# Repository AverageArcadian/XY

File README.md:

# XY
ESP32 based XY motion controller for laser or plotting based machines

view here - https://kicanvas.org/?github=https%3A%2F%2Fgithub.com%2FAverageArcadian%2FXY

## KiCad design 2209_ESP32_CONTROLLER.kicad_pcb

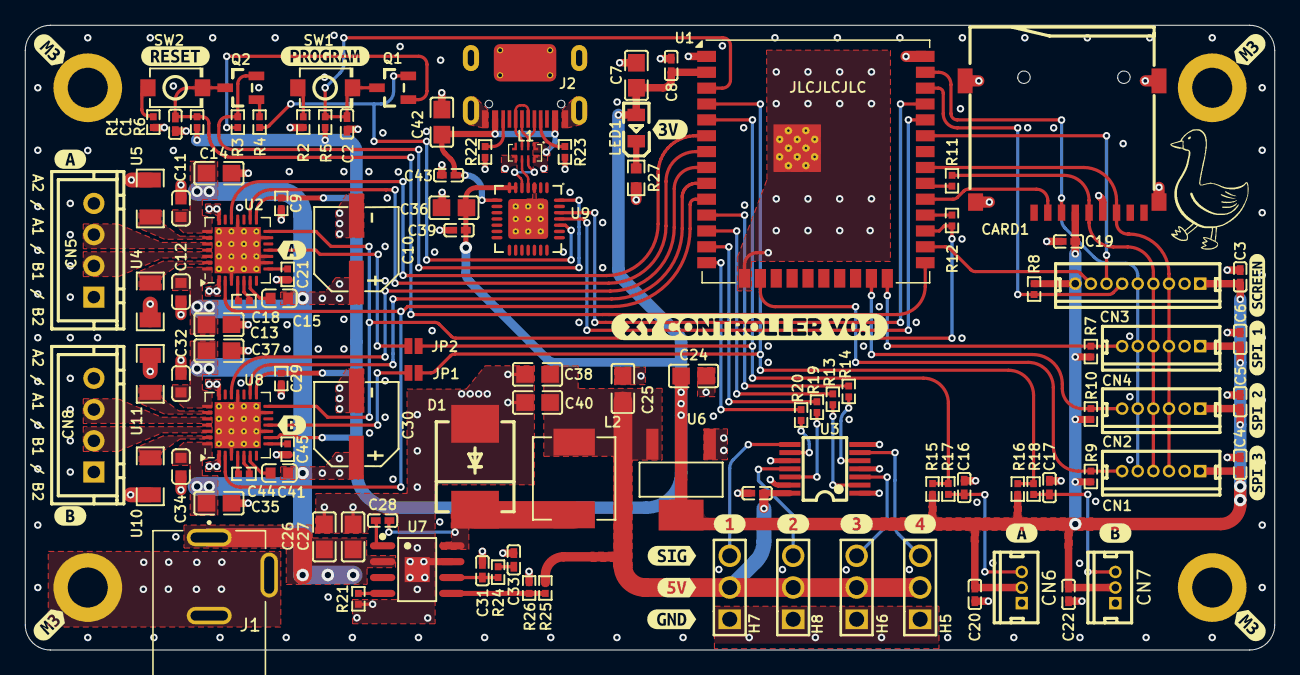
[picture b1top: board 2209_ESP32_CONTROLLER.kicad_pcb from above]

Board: 4 copper layers, 100.0 x 50.0 mm, 137 parts (0 on the bottom side), 84 nets.

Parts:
C1, C2, C3, C4, C5, C6, C8, C16, C17, C19, C20, C22, C23, C28, C39, C43: 100nF; C0402
C7, C13, C14, C24, C25, C35, C36, C37, C42: 10uF; C0805
C9, C29: 100nF; R0402
C10, C30: 100uF; CAP-SMD_BD6.3-L6.6-W6.6-LS7.6-RD
C11, C12, C15, C32, C34, C41: 100nF; C0603
C18, C44: 22nF; R0402
C21, C45: 4.7uF; R0402
C26, C27: 2.2uF; C0805
C31: 39pF; C0402
C33: 6.8nF; C0402
C38, C40: 47nF; C0805
CARD1: TF-SMD_TF-01A
CN1, CN2, CN4: CONN-TH_1.25T-6A
CN3: CONN-TH_1.25T-9A
CN5, CN8: CONN-TH_4P-P2.50_XH-4A
CN6, CN7: CONN-TH_1.25T-3A
D1: SMC_L7.1-W6.2-LS8.1-RD
H1, H2, H3, H4: MISC_PARTS:MountingHole_3.2mm_M3_ISO14580_Pad; MountingHole_3.2mm_M3_ISO14580_Pad
H5, H6, H7, H8: HDR-TH_3P-P2.54-V-M-1
J1: 54-00167; TENSILITY_54-00167
J2: Connector, USB-TYPE-C-16P; TYPE-C-SMD_HX-TYPE-C-16PIN
JP1, JP2: Jumper_2_NO_NoSilk
L1: QFN-8_L2.5-W1.2-P0.50-BL
L2: 10uH; IND-SMD_L7.1-W6.6
LED1: LED0805-R-RD
Q1, Q2: TO-236-3_L2.9-W1.3-P1.90-LS2.4-BR
R1, R2, R12, R13, R14, R19, R20: 1kΩ; R0402
R3, R4, R5, R6, R7, R8, R9, R10, R15, R16: 10kΩ; R0402
R11: 22Ω; R0402
R17, R18, R21: 100kΩ; R0402
R22, R23: 5.1kΩ; R0402
R24: 13kΩ; R0402
R25: 270kΩ; R0402
R26: 51kΩ; R0402
R27: 4.02kΩ; R0603
SW1, SW2: SW-SMD_L3.9-W3.0-P4.45
U1: ESP32-WROOM-32UE
U2, U8: TMC2209-LA; VQFN-28-1EP_5x5mm_P0.5mm_EP3.7x3.7mm_ThermalVias
U3: TSSOP-14_L5.0-W4.4-P0.65-LS6.4-BL
U4, U5, U10, U11: 100mΩ; R1206
U6: SOT-223-4_L6.5-W3.5-P2.30-LS7.0-BR
U7: SOIC-8_L5.0-W4.0-P1.27-LS6.0-BL-EP2.0
U9: CP2102-GMR; WQFN-28_L5.0-W5.0-P0.50-BL-EP3.2
kibuzzard-683B1B8C: G***; kibuzzard-683B1B8C
kibuzzard-683FCDE9: G***; kibuzzard-683FCDE9
kibuzzard-683FD1C3: G***; kibuzzard-683FD1C3
kibuzzard-683FD1D9: G***; kibuzzard-683FD1D9
kibuzzard-6843B2AB: G***; kibuzzard-6843B2AB
kibuzzard-6843B2BA: G***; kibuzzard-6843B2BA
kibuzzard-6843B9D2: G***; kibuzzard-6843B9D2
kibuzzard-6843B9E6: G***; kibuzzard-6843B9E6
kibuzzard-6843B9EA: G***; kibuzzard-6843B9EA
kibuzzard-6843B9F5: G***; kibuzzard-6843B9F5
kibuzzard-6843B298: G***; kibuzzard-6843B298
kibuzzard-68384F2C: G***; kibuzzard-68384F2C
kibuzzard-68384F55: G***; kibuzzard-68384F55
kibuzzard-68384F99: G***; kibuzzard-68384F99
kibuzzard-68384FEC: G***; kibuzzard-68384FEC
kibuzzard-682550E8: G***; kibuzzard-682550E8
kibuzzard-6845247B, kibuzzard-6845247B#2: G***; kibuzzard-6845247B
kibuzzard-68255129: G***; kibuzzard-68255129
kibuzzard-68450460: G***; kibuzzard-68450460
kibuzzard-68450470: G***; kibuzzard-68450470
kibuzzard-68450480: G***; kibuzzard-68450480
kibuzzard-68450486: G***; kibuzzard-68450486
kibuzzard-68452487, kibuzzard-68452487#2: G***; kibuzzard-68452487

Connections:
+3.3V: C3.1, C4.1, C5.1, C6.1, C7.2, C8.2, C9.1, C19.1, C20.1, C22.1, C24.1, C29.1, C36.1, C39.1, CARD1.4 (VDD), CN1.1, CN2.1, CN3.1, CN3.9, CN4.1, CN6.2, CN7.2, LED1.1 (+), R5.1, R6.1, R7.1, R8.1, R9.1, R10.1, R15.1, R16.1, U1.2 (VDD), U2.15 (VCC_IO), U6.2 (Output), U6.4 (Output), U8.9 (MS1/AD0), U8.15 (VCC_IO), U9.6 (VDD), U9.7 (REGIN)
+5V: C23.1, C25.1, C38.2, C40.2, H5.2, H6.2, H7.2, H8.2, L2.2, R25.1, U3.14 (VCC), U6.3 (Input)
+24V: C10.1, C11.1, C12.1, C13.1, C14.1, C15.1, C26.1, C27.1, C30.1, C32.1, C34.1, C35.1, C37.1, C41.1, J1.A, U2.22 (VS), U2.28 (VS), U7.2 (VIN), U8.22 (VS), U8.28 (VS)
/Rx: R12.1, U1.28 (IO17)
CLK: CARD1.5 (CLK(SCLK)), CN1.4, CN2.4, CN3.4, CN4.4, R11.2
CS_SD: CARD1.2 (CDDAT3(CS)), U1.29 (IO5)
DTR: Q2.2 (E), R3.1, U9.28 (DTR)
ESP32_EN: C2.1, Q1.3 (C), R5.2, SW1.2, U1.3 (EN)
GND: C1.2, C2.2, C3.2, C4.2, C5.2, C6.2, C7.1, C8.1, C9.2, C10.2, C11.2, C12.2, C13.2, C14.2, C16.2, C17.2, C19.2, C20.2, C21.2, C22.2, C23.2, C24.2, C25.2, C26.2, C27.2, C29.2, C30.2, C31.1, C32.2, C33.2, C34.2, C35.2, C36.2, C37.2, C38.1, C39.2, C40.1, C42.2, C43.2, C45.2, CARD1.6 (VSS), CARD1.10 (GND), CARD1.11 (GND), CARD1.12 (GND), CARD1.13 (GND), CN1.2, CN2.2, CN3.2, CN4.2, CN6.1, CN7.1, D1.2 (A), H1.1, H2.1, H3.1, H4.1, H5.1, H6.1, H7.1, H8.1, J1.B, J1.C, J2.A12B1 (GND), J2.B12A1 (GND), J2.S1 (SHIELD), L1.5 (GND), L1.8 (GND), R1.2, R2.2, R21.2, R22.2, R23.2, R26.2, R27.1, U1.1 (GND), U1.15 (GND), U1.38 (GND), U1.39 (GND), U2.3 (GND), U2.9 (MS1/AD0), U2.10 (MS2/AD1), U2.13 (CLK), U2.18 (GND), U2.29 (GND), U3.1 (1OE#), U3.4 (2OE#), U3.7 (GND), U3.10 (3OE#), U3.13 (4OE#), U4.1, U5.1, U6.1 (GND/ADJ), U7.7 (GND), U7.9 (EP), U8.3 (GND), U8.10 (MS2/AD1), U8.13 (CLK), U8.18 (GND), U8.29 (GND), U9.3 (GND), U9.29 (EP), U10.1, U11.1
GPIO_0: C1.1, Q2.3 (C), R6.2, SW2.2, U1.25 (IO0)
GPIO_2: CN4.6, R7.2, U1.24 (IO2)
GPIO_11: R14.1, U1.11 (IO26)
GPIO_12: R20.2, U1.14 (IO12)
GPIO_14: R19.2, U1.13 (IO14)
GPIO_15: CN2.6, R10.2, U1.23 (IO15)
GPIO_16: CN1.6, R9.2, U1.16 (IO13)
GPIO_22: CN3.6, R8.2, U1.36 (IO22)
GPIO_27: R13.1, U1.12 (IO27)
LCD_D/C: CN3.7, U1.33 (IO21)
LCD_RST: CN3.8, U1.26 (IO4)
MISO: CARD1.7 (DAT0(D0)), CN1.3, CN2.3, CN3.3, CN4.3, U1.31 (IO19)
MOSI: CARD1.3 (CMD(DI)), CN1.5, CN2.5, CN3.5, CN4.5, U1.37 (IO23)
unnamed: C16.1, CN6.3, R17.2
unnamed: C17.1, CN7.3, R18.2
unnamed: C33.1, R24.1
unnamed: C28.2, D1.1 (K), L2.1, U7.8 (SW)
unnamed: J2.A5 (CC1), R23.1
unnamed: J2.B5 (CC2), R22.1
unnamed: J2.A6 (D+), J2.B6 (D+), L1.3 (D+)
unnamed: J2.A7 (D-), J2.B7 (D-), L1.2 (D-)
unnamed: LED1.2 (-), R27.2
unnamed: Q1.1 (B), R3.2
unnamed: Q2.1 (B), R4.2
unnamed: R1.1, SW2.1
unnamed: R2.1, SW1.1
unnamed: R11.1, U1.30 (IO18)
unnamed: C21.1, U2.8 (5VOUT)
unnamed: U2.23 (BRA), U5.2
unnamed: U2.27 (BRB), U4.2
unnamed: C18.2, U2.5 (CPI)
unnamed: C18.1, U2.4 (CPO)
unnamed: CN5.3, U2.24 (OA1)
unnamed: CN5.4, U2.21 (OA2)
unnamed: CN5.2, U2.26 (OB1)
unnamed: CN5.1, U2.1 (OB2)
unnamed: C15.2, U2.6 (VCP)
unnamed: R13.2, U3.2 (1A)
unnamed: H6.3, U3.3 (1Y)
unnamed: R14.2, U3.5 (2A)
unnamed: H5.3, U3.6 (2Y)
unnamed: R20.1, U3.9 (3A)
unnamed: H7.3, U3.8 (3Y)
unnamed: R19.1, U3.12 (4A)
unnamed: H8.3, U3.11 (4Y)
unnamed: C28.1, U7.1 (BOOT)
unnamed: C31.2, R24.2, U7.6 (COMP)
unnamed: R25.2, R26.1, U7.5 (FB)
unnamed: R21.1, U7.4 (RT/CLK)
unnamed: C45.1, U8.8 (5VOUT)
unnamed: U8.23 (BRA), U11.2
unnamed: U8.27 (BRB), U10.2
unnamed: C44.2, U8.5 (CPI)
unnamed: C44.1, U8.4 (CPO)
unnamed: CN8.3, U8.24 (OA1)
unnamed: CN8.4, U8.21 (OA2)
unnamed: CN8.2, U8.26 (OB1)
unnamed: CN8.1, U8.1 (OB2)
unnamed: C41.2, U8.6 (VCP)
unnamed: L1.6 (D+), U9.4 (D+)
unnamed: L1.7 (D-), U9.5 (D-)
RTS: Q1.2 (E), R4.1, U9.24 (RTS)
RXD0: U1.34 (RXD0/IO3), U9.25 (RXD)
STEP_DISABLE: U1.10 (IO25), U2.2 (~EN), U8.2 (~EN)
TMC_UART: R12.2, U1.27 (IO16), U2.14 (~PD/UART), U8.14 (~PD/UART)
TXD0: U1.35 (TXD0/IO1), U9.26 (TXD)
VBUS: C42.1, C43.1, J2.A9B4 (VBUS), J2.B9A4 (VBUS), L1.1 (VBUS), U9.8 (VBUS)
VN: JP2.2 (B), R15.2, R17.1, U1.5 (SENSOR_VN)
VP: JP1.2 (B), R16.2, R18.1, U1.4 (SENSOR_VP)
X_DIAG: JP2.1 (A), U2.11 (DIAG)
X_DIR: U1.6 (IO34), U2.19 (DIR)
X_STEP: U1.7 (IO35), U2.16 (STEP)
Y_DIAG: JP1.1 (A), U8.11 (DIAG)
Y_DIR: U1.8 (IO32), U8.19 (DIR)
Y_STEP: U1.9 (IO33), U8.16 (STEP)
